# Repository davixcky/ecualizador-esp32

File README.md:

# Ecualizador de audio de tres bandas con ESP32

## Prototipo en protoboard

[Guía de montaje y esquema (PDF)](docs/protoboard/guia-prototipo-protoboard.pdf) · [Lista de materiales (CSV)](docs/protoboard/materiales.csv) · [Conexiones pin por pin (CSV)](docs/protoboard/conexiones.csv). Incluye pruebas con generador y osciloscopio, y ampliación con ESP32, pantalla y NeoPixel. [Fuente LaTeX](docs/latex/prototipo-protoboard.tex).

## Video del dispositivo

[Ver video en Full HD](docs/video/ecualizador-animado.mp4) · [Escena de Blender y texturas](docs/video/ecualizador-blender.zip). Demo de 36 segundos con sonido: los deslizadores cambian el audio usando las respuestas SPICE del circuito. Pantalla y luces sincronizadas; apertura de la tapa imantada. Es una demo virtual, no una grabación del prototipo físico.

Proyecto de Electrónica II · Universidad de la Costa · Leo Rojas, David Orozco y Manuel Castilla.

La ruta de audio usa filtros activos y controles analógicos. El ESP32 lee los niveles y calcula una FFT para la pantalla Waveshare de **1,9 pulgadas, 170 × 320, ST7789V2**. El gabinete EQ / 03 tiene acabado grafito, cierre con cuatro pares de imanes y dos canales interiores para 12 NeoPixel.

| Entrega | Archivos actuales |
|---|---|
| Presentación en LaTeX | [PDF](docs/presentacion/presentacion-fase2.pdf) · [PowerPoint con notas](docs/presentacion/presentacion-fase2.pptx) · [PDF con notas](docs/presentacion/presentacion-notas.pdf) |
| Exposición con animaciones | [PowerPoint animado](docs/presentacion/presentacion-animada.pptx) · [PDF por pasos](docs/presentacion/presentacion-animada.pdf) · [Cómo presentar](docs/presentacion/LEEME.md) |
| Informe | [PDF](docs/informe-fase2.pdf) · [Word](docs/informe-fase2.docx) · [Markdown](docs/informe-fase2.md) |
| Fuentes editables en LaTeX | [Informe](docs/latex/informe.tex) · [Presentación Beamer](docs/latex/presentacion.tex) |
| Presentación corta de filtros | [PDF de 10 diapositivas](docs/presentacion/presentacion-filtros-hoy.pdf) · [PowerPoint con notas](docs/presentacion/presentacion-filtros-hoy.pptx) · [Fuente LaTeX](docs/latex/presentacion-filtros.tex) |
| Ensayo de hoy | [Generador y osciloscopio: guía](simulacion/velxio/DEMO-HOY.md) |
| Paquete para otro computador | [ZIP portátil: presentación, esquema y simulaciones](docs/exposicion-portable.zip) |
| Simulación en Velxio | [Abrir casos locales](simulacion/velxio/index.html) · [Instrucciones y alcance](simulacion/velxio/README.md) · [100 Hz](simulacion/velxio/filtros-100Hz.vlx) · [1 kHz](simulacion/velxio/filtros-1000Hz.vlx) · [8 kHz](simulacion/velxio/filtros-8000Hz.vlx) |
| Esquemático | [PDF](hardware/ecualizador.pdf) · [KiCad](hardware/ecualizador.kicad_sch) · [ERC](hardware/erc.rpt) |
| PCB de una cara D.2 | [Plano PDF](hardware/pcb-rev-D2.pdf) · [KiCad](hardware/ecualizador.kicad_pcb) · [DRC](hardware/drc.rpt) · [Montaje y puentes](hardware/una-cara/LEEME.md) · [BOM](hardware/fabricacion/bom.csv) |
| Modelos 3D | [Gabinete STEP](cad/ecualizador-gabinete.step) · [Piezas STL](cad/stl/) · [PCB STEP](hardware/3d/ecualizador-placa.step) · [PCB VRML](hardware/3d/ecualizador-placa.wrl) |
| Propuesta original y rúbrica | [Fase 1](docs/fase1/) |

## Estado de la revisión del 22 de octubre de 2026

- ERC: cero errores y cero advertencias. Las 59 redes coinciden pin a pin con la definición del circuito.
- DRC D.2: cero infracciones, cero pads sin conectar y cero diferencias con el esquema. El DRC comprueba las 59 redes mediante cobre inferior, plano de GND y 80 cables. Las comprobaciones y límites de montaje se documentan en [la guía](hardware/una-cara/LEEME.md).
- ngspice: 23 casos del diseño revisado cumplen sus criterios. El caso histórico de Fase 1 reproduce el valle que motivó la corrección. El macromodelo del operacional es una aproximación propia.
- Velxio: tres proyectos ejecutados con motor SPICE; predominan graves a 100 Hz, medios a 1 kHz y agudos a 8 kHz. Los filtros usan operacionales ideales. Un cuarto [ensayo animado de 12 NeoPixel](simulacion/velxio/led-animado.vlx) ejecuta código del ESP32; usa un patrón programado sin audio.
- Velxio integrado: entrada → filtros → detectores → ADC ESP32 → TFT ILI9341, usando QEMU. Se comprueba el predominio de cada banda con 100 Hz, 1 kHz y 8 kHz. FFT sin calibración de frecuencia; no incluye potencia ni adaptación LED. [Guía y modelos](simulacion/velxio/INTEGRADO.md).
- Firmware: compilación ESP32 correcta; 19 comprobaciones DSP y cinco comparaciones de dibujo por franjas correctas en el computador.
- El montaje físico, las mediciones con instrumentos y el requisito de más del 70 % de dispositivos adquiridos y conectados **siguen sin evidencia en este repositorio**.

Los [registros de validación](docs/validacion/) conservan los resultados. Los renders provienen del CAD y de KiCad; las pantallas se dibujan con el código de interfaz y datos de ejemplo.

## Pantalla e iluminación

J4 es un adaptador de ocho señales a 2,54 mm, no la huella GH1.25 de Waveshare. Conectar por **nombre de señal**, siguiendo la tabla del informe: VCC, GND, DIN, CLK, CS, DC, RST y BL. La interfaz trabaja en horizontal a 320 × 170.

GPIO25 controla la tira mediante un 74AHCT125 y 330 Ω. J5 lleva 5 V, DIN y GND. Se prevén dos tramos de 100 mm, seis LED por tramo, y canales de 102 × 10,6 × 3 mm con difusores. El brillo inicial es 32/255, fijo. La fuente prevista es de 5 V / 3 A por J6; **desconectar VBUS del USB cuando se usa esa fuente**. No alimentar los LED desde 3,3 V ni usar VREF como retorno.

## Reproducir los archivos

Los PDF usan el logo oficial CUC, rojo institucional y Red Hat Display, según el [manual consultado](img/marca/README.md). Las fuentes vigentes son los `.tex` (LuaLaTeX). El PowerPoint contiene imágenes de las diapositivas y notas; el texto se edita en LaTeX. El HTML anterior está archivado en `docs/archivo/`.

```sh
# TeX Live: latex-extra, lang-spanish, fonts-recommended, luatex; pandoc
# Python: pymupdf, python-pptx (para exportar PNG y PowerPoint)
bash herramientas/compilar_documentos.sh

# Firmware y pruebas en computador
pio run -d firmware
make -C firmware/test prueba pantallas

# Conectividad y simulación (ngspice, numpy, matplotlib)
python3 herramientas/verificar_netlist.py
.venv/bin/python herramientas/simulacion.py

# PCB de una cara: regenerar y verificar
python3 herramientas/generar_esquematico.py
python3 herramientas/generar_pcb.py
bash herramientas/exportar_fabricacion.sh

# CAD (CadQuery) y renders (Blender, KiCad)
.venv/bin/python herramientas/validar_cad.py
bash cad/generar.sh

# Repetir la comprobación web (Node y Playwright con Chromium)
node herramientas/validar_velxio.cjs
node herramientas/validar_led_velxio.cjs
```

Las vistas de ensamblaje y colores de bandas parten de C2-ABPR; la revisión EQ / 03 adopta acabado grafito, rotulación compacta y cierre magnético. Las cotas de pantalla, controles y conectores deben contrastarse con las piezas adquiridas antes de imprimir y montar.

La presentación incluye fragmentos del esquema real para explicar preamplificador, Sallen-Key, sumador y detector. Los PDF adjuntan el esquema, el plano D.2 y los proyectos Velxio. El enlace y el QR abren el editor; después se importa el caso `.vlx`. Ver [cierre magnético y cotas](cad/CIERRE-MAGNETICO.md).

La PCB D.2 organiza las etapas con el flujo Python/KiCad y Freerouting de medidor-energia-esp32: ESP32 a la derecha, operacionales por etapas y cableado identificado por colores. Usa una sola cara de cobre y puentes aislados. Los controles van en el panel y requieren las [cabeceras y cables de montaje](hardware/una-cara/LEEME.md). Los Gerbers de dos capas B.1 están archivados y no corresponden al montaje vigente.

### Placa única E.2 (propuesta, 33 alambres)

[E.2](hardware/E2-placa-unica/README.md) reduce los 80 tramos de D.2 a 33 alambres en una sola placa de una cara de 200 × 120 mm para el gabinete original. Usa plano de GND, componentes con las patas más abiertas para pasar pistas por debajo, y reasigna las secciones de los amplificadores y los GPIO. El firmware se compila con `pio run -e e2`. La alternativa de tres placas está en [E.1](hardware/E1-tres-placas/README.md).

### Montaje de los puentes

La cara superior lleva 29 puentes cortos (hasta 20 mm entre extremos). Los 51 cables restantes se montan aislados por debajo. El total sigue siendo 80 tramos; no se añade una capa de cobre. [La guía](hardware/PUENTES.md) y [el plano de cuatro páginas](hardware/pcb-rev-D2.pdf) indican la cara de cada conexión. Los arcos del render son orientativos: el montaje requiere comprobar separación, sujeción y continuidad.

### Prototipo de laboratorio con TL072CP (±12 V)

Para el montaje con los integrados disponibles: [guía PDF](docs/prototipo-tl072/guia-prototipo-TL072.pdf), [fuente LaTeX](docs/latex/prototipo-tl072.tex) y [paquete de conexiones y simulación](docs/prototipo-tl072/prototipo-TL072.zip). Utiliza cuatro TL072, salida de línea y medidas a 100 Hz, 1 kHz y 8 kHz. Es una variante analógica independiente del diseño MCP6004 de 3,3 V; sus salidas no se conectan directamente al ESP32.

Esquema completo del prototipo en una lámina A2: [PDF](docs/prototipo-tl072/esquema-completo-TL072.pdf) · [SVG editable](docs/prototipo-tl072/esquema-completo.svg). Incluido al final de la guía TL072.

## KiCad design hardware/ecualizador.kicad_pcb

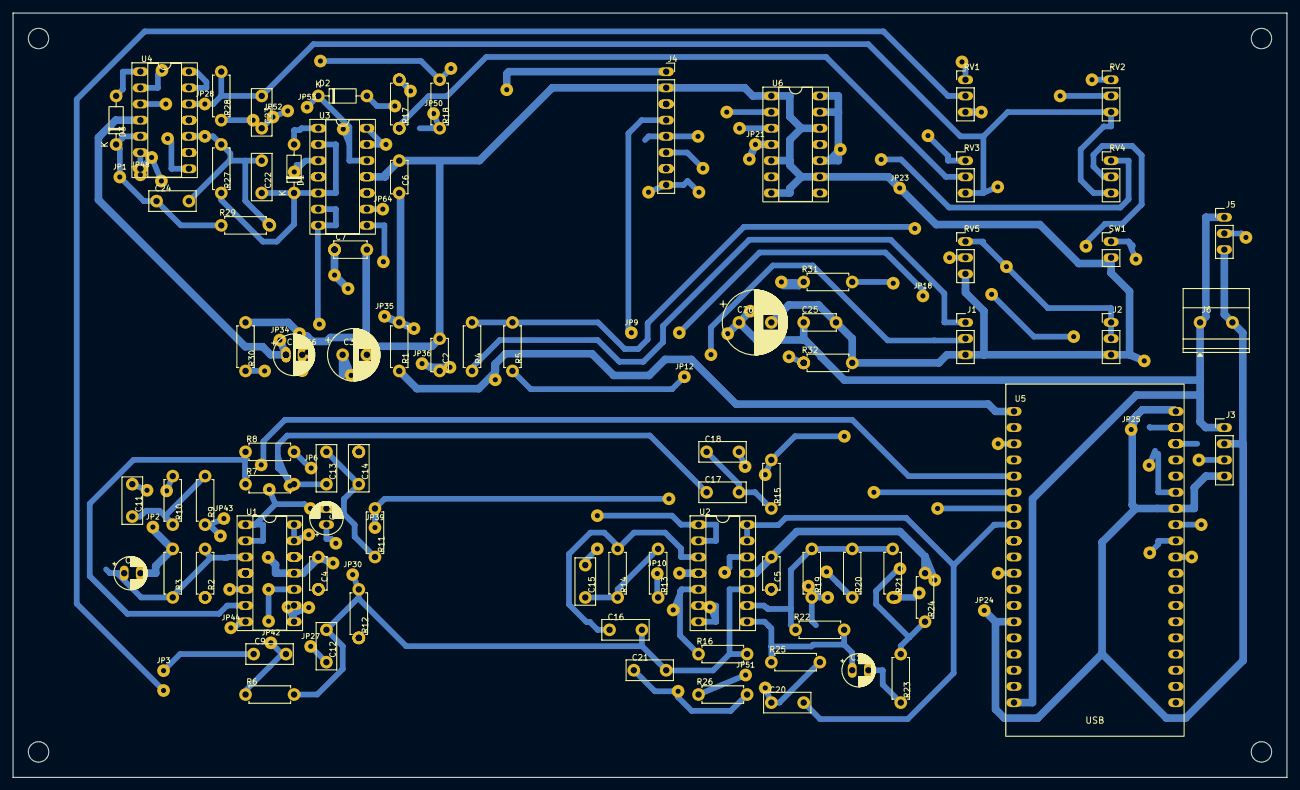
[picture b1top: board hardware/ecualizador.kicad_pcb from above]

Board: 2 copper layers, 200.0 x 120.0 mm, 162 parts (0 on the bottom side), 59 nets.

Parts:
C1: 100u 10V; UnaCara_C1
C2: 100n; UnaCara_C2
C3: 470u 10V; UnaCara_C3
C4: 100n; UnaCara_C4
C5: 100n; UnaCara_C5
C6: 100n; UnaCara_C6
C7: 100n; UnaCara_C7
C8: 10u 16V; UnaCara_C8
C9: 1u film; UnaCara_C9
C10: 10u 16V; UnaCara_C10
C11: 100n film; UnaCara_C11
C12: 47n film; UnaCara_C12
C13: 10n film; UnaCara_C13
C14: 10n film; UnaCara_C14
C15: 10n film; UnaCara_C15
C16: 4n7 film; UnaCara_C16
C17: 10n film; UnaCara_C17
C18: 10n film; UnaCara_C18
C19: 10u 16V; UnaCara_C19
C20: 4n7 film; UnaCara_C20
C21: 2n2 film; UnaCara_C21
C22: 100n film; UnaCara_C22
C23: 100n film; UnaCara_C23
C24: 100n film; UnaCara_C24
C25: 100n; UnaCara_C25
C26: 1000u 10V; UnaCara_C26
D1: 1N4148; UnaCara_D1
D2: 1N4148; UnaCara_D2
D3: 1N4148; UnaCara_D3
H1, H2, H3, H4: MountingHole_3.2mm_M3
J1: Entrada de línea 3,5 mm; UnaCara_J1
J2: Salida de línea 3,5 mm; UnaCara_J2
J3: PAM8403; UnaCara_J3
J4: Waveshare 1.9 ST7789V2; UnaCara_J4
J5: NeoPixel 5V DIN GND; UnaCara_J5
J6: Entrada 5V 3A; UnaCara_J6
JP1, JP2, JP3, JP4, JP5, JP6, JP7, JP8, JP9, JP10, JP11, JP12, JP13, JP14, JP15, JP16, JP17, JP18, JP19, JP20, JP21, JP22, JP23, JP24, JP25, JP26, JP27, JP28, JP29, JP30, JP31, JP32, JP33, JP34, JP35, JP36, JP37, JP38, JP39, JP40, JP41, JP42, JP43, JP44, JP45, JP46, JP47, JP48, JP49, JP50, JP51, JP52, JP53, JP54, JP55, JP56, JP57, JP58, JP59, JP60, JP61, JP62, JP63, JP64, JP65, JP66: Puente aislado
JP67, JP68, JP69, JP70, JP71, JP72, JP73, JP74, JP75, JP76, JP77, JP78, JP79: Puente a terminal
R1: 10; UnaCara_R1
R2: 10k 1%; UnaCara_R2
R3: 10k 1%; UnaCara_R3
R4: 10k; UnaCara_R4
R5: 10k; UnaCara_R5
R6: 100k; UnaCara_R6
R7: 22k 1%; UnaCara_R7
R8: 10k 1%; UnaCara_R8
R9: 10k 1%; UnaCara_R9
R10: 10k 1%; UnaCara_R10
R11: 27k 1%; UnaCara_R11
R12: 56k 1%; UnaCara_R12
R13: 10k 1%; UnaCara_R13
R14: 10k 1%; UnaCara_R14
R15: 2k7 1%; UnaCara_R15
R16: 5k6 1%; UnaCara_R16
R17: 47k 1%; UnaCara_R17
R18: 47k 1%; UnaCara_R18
R19: 47k 1%; UnaCara_R19
R20: 47k 1%; UnaCara_R20
R21: 47k 1%; UnaCara_R21
R22: 100k 1%; UnaCara_R22
R23: 100; UnaCara_R23
R24: 47k; UnaCara_R24
R25: 10k 1%; UnaCara_R25
R26: 10k 1%; UnaCara_R26
R27: 220k; UnaCara_R27
R28: 220k; UnaCara_R28
R29: 220k; UnaCara_R29
R30: 10k; UnaCara_R30
R31: 330; UnaCara_R31
R32: 10k; UnaCara_R32
RV1: 10k log; UnaCara_RV1
RV2: 10k lin; UnaCara_RV2
RV3: 10k lin; UnaCara_RV3
RV4: 10k lin; UnaCara_RV4
RV5: 10k log; UnaCara_RV5
SW1: Pulsador; UnaCara_SW1
U1: MCP6004; UnaCara_U1
U2: MCP6004; UnaCara_U2
U3: MCP6004; UnaCara_U3
U4: MCP6004; UnaCara_U4
U5: ESP32-DevKitC V4; UnaCara_U5
U6: 74AHCT125; UnaCara_U6

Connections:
+3.3VA: C1.1, C2.1, C4.1, C5.1, C6.1, C7.1, JP34.1, JP35.1, JP36.1, JP37.1, JP70.1, JP71.1, JP72.1, JP73.1, JP74.1, R1.2, R2.1, U1.4, U2.4, U3.4, U4.4
+3V3: J4.1, JP54.1, R1.1, U5.1
+5V: C3.1, C25.1, C26.1, J3.1, J5.1, J6.1, JP20.1, JP21.1, JP63.1, U5.19, U6.4, U6.10, U6.13, U6.14
/ADC_A: JP48.1, JP49.1, U4.6, U4.7, U5.7
/ADC_FFT: C20.2, U2.13, U2.14, U5.8
/ADC_G: JP5.1, U3.6, U3.7, U5.5
/ADC_M: JP60.1, U3.13, U3.14, U5.6
/AGUDOS: JP13.1, JP33.1, R15.2, RV4.1, U2.6, U2.7
/AMP_IN: J3.3, JP38.1, RV5.2
/A_W: JP17.1, JP40.1, R21.1, RV4.2, U4.3
/BTN: JP62.1, SW1.1, U5.11
/EQ_OUT: C19.1, R22.2, R25.1, U2.8
/GRAVES: C11.2, JP45.1, JP46.1, RV2.1, U1.8, U1.9
/G_W: JP59.1, JP65.1, R19.1, RV2.2, U3.3
/IN_L: J1.T, R4.1
/IN_R: J1.R, JP12.1, R5.1
/LED_5V: JP47.1, R31.1, U6.3
/LED_DATA: JP61.1, JP76.1, R32.1, U5.9, U6.2
/LED_DIN: J5.2, JP14.1, R31.2
/LINEA: J2.R, J2.T, JP15.1, R23.2, R24.1, RV5.1
/MEDIOS: C15.2, JP8.1, RV3.1, U2.1, U2.2
/MED_HP: JP10.1, JP39.1, R11.2, R13.1, U1.13, U1.14
/M_INV: JP4.1, JP32.1, R18.2, R20.1, U4.8
/M_W: JP77.1, R17.1, RV3.2, U3.10
/PRE: C13.1, C17.1, JP43.1, JP44.1, R7.2, R9.1, U1.7
/TFT_BL: J4.8, JP57.1, JP58.1, R30.1, U5.27
/TFT_CS: J4.5, JP55.1, U5.29
/TFT_DC: J4.6, JP56.1, U5.25
/TFT_MOSI: J4.3, JP78.1, U5.21
/TFT_RST: J4.7, JP79.1, U5.22
/TFT_SCK: J4.4, JP9.1, JP18.1, JP19.1, U5.28
/VREF: C10.2, C12.2, C16.2, C21.2, C22.2, C23.2, C24.2, JP28.1, JP29.1, JP30.1, JP31.1, R6.2, R12.2, R16.2, R27.2, R28.2, R29.2, RV2.3, RV3.3, RV4.3, U1.1, U1.2, U2.10, U4.10, U4.12, U5.3
GND: C1.2, C2.2, C3.2, C4.2, C5.2, C6.2, C7.2, C8.2, C25.2, C26.2, J1.S, J2.S, J3.2, J3.4, J4.2, J5.3, J6.2, JP2.1, JP22.1, JP23.1, JP24.1, JP25.1, JP66.1, JP67.1, R3.2, R24.2, R30.2, R32.2, RV1.3, RV5.3, SW1.2, U1.11, U2.11, U3.11, U4.11, U5.14, U5.20, U5.26, U6.1, U6.5, U6.7, U6.9, U6.12
unnamed: C9.1, JP3.1, RV1.2
unnamed: C10.1, JP6.1, R8.2
unnamed: C11.1, R9.2, R10.1
unnamed: C13.2, C14.1, R11.1
unnamed: C15.1, R13.2, R14.1
unnamed: C17.2, C18.1, R15.1
unnamed: C19.2, R23.1
unnamed: C20.1, JP51.1, R25.2, R26.1
unnamed: D1.2, U3.1
unnamed: C22.1, D1.1, R27.1, U3.2, U3.5
unnamed: D2.2, JP7.1, U3.8
unnamed: C23.1, D2.1, JP52.1, JP53.1, JP64.1, R28.1, U3.9, U3.12
unnamed: D3.2, U4.1
unnamed: C24.1, D3.1, JP1.1, R29.1, U4.2, U4.5
unnamed: JP16.1, R4.2, R5.2, RV1.1
unnamed: C8.1, R2.2, R3.1, U1.3
unnamed: C9.2, JP42.1, R6.1, U1.5
unnamed: R7.1, R8.1, U1.6
unnamed: C12.1, JP26.1, JP27.1, R10.2, U1.10
unnamed: C14.2, JP68.1, JP69.1, R12.1, U1.12
unnamed: C16.1, R14.2, U2.3
unnamed: C18.2, JP41.1, R16.1, U2.5
unnamed: R19.2, R20.2, R21.2, R22.1, U2.9
unnamed: C21.1, JP11.1, R26.2, U2.12
unnamed: JP50.1, JP75.1, R17.2, R18.1, U4.9
unnamed: U4.13, U4.14

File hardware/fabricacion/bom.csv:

"Reference","Value","Footprint","QUANTITY"
"C1","100u 10V","Ecualizador:UnaCara_C1","1"
"C2","100n","Ecualizador:UnaCara_C2","1"
"C3","470u 10V","Ecualizador:UnaCara_C3","1"
"C4","100n","Ecualizador:UnaCara_C4","1"
"C5","100n","Ecualizador:UnaCara_C5","1"
"C6","100n","Ecualizador:UnaCara_C6","1"
"C7","100n","Ecualizador:UnaCara_C7","1"
"C8","10u 16V","Ecualizador:UnaCara_C8","1"
"C9","1u film","Ecualizador:UnaCara_C9","1"
"C10","10u 16V","Ecualizador:UnaCara_C10","1"
"C11","100n film","Ecualizador:UnaCara_C11","1"
"C12","47n film","Ecualizador:UnaCara_C12","1"
"C13","10n film","Ecualizador:UnaCara_C13","1"
"C14","10n film","Ecualizador:UnaCara_C14","1"
"C15","10n film","Ecualizador:UnaCara_C15","1"
"C16","4n7 film","Ecualizador:UnaCara_C16","1"
"C17","10n film","Ecualizador:UnaCara_C17","1"
"C18","10n film","Ecualizador:UnaCara_C18","1"
"C19","10u 16V","Ecualizador:UnaCara_C19","1"
"C20","4n7 film","Ecualizador:UnaCara_C20","1"
"C21","2n2 film","Ecualizador:UnaCara_C21","1"
"C22","100n film","Ecualizador:UnaCara_C22","1"
"C23","100n film","Ecualizador:UnaCara_C23","1"
"C24","100n film","Ecualizador:UnaCara_C24","1"
"C25","100n","Ecualizador:UnaCara_C25","1"
"C26","1000u 10V","Ecualizador:UnaCara_C26","1"
"D1","1N4148","Ecualizador:UnaCara_D1","1"
"D2","1N4148","Ecualizador:UnaCara_D2","1"
"D3","1N4148","Ecualizador:UnaCara_D3","1"
"J1","Entrada de línea 3,5 mm","Ecualizador:UnaCara_J1","1"
"J2","Salida de línea 3,5 mm","Ecualizador:UnaCara_J2","1"
"J3","PAM8403","Ecualizador:UnaCara_J3","1"
"J4","Waveshare 1.9 ST7789V2","Ecualizador:UnaCara_J4","1"
"J5","NeoPixel 5V DIN GND","Ecualizador:UnaCara_J5","1"
"J6","Entrada 5V 3A","Ecualizador:UnaCara_J6","1"
"R1","10","Ecualizador:UnaCara_R1","1"
"R2","10k 1%","Ecualizador:UnaCara_R2","1"
"R3","10k 1%","Ecualizador:UnaCara_R3","1"
"R4","10k","Ecualizador:UnaCara_R4","1"
"R5","10k","Ecualizador:UnaCara_R5","1"
"R6","100k","Ecualizador:UnaCara_R6","1"
"R7","22k 1%","Ecualizador:UnaCara_R7","1"
"R8","10k 1%","Ecualizador:UnaCara_R8","1"
"R9","10k 1%","Ecualizador:UnaCara_R9","1"
"R10","10k 1%","Ecualizador:UnaCara_R10","1"
"R11","27k 1%","Ecualizador:UnaCara_R11","1"
"R12","56k 1%","Ecualizador:UnaCara_R12","1"
"R13","10k 1%","Ecualizador:UnaCara_R13","1"
"R14","10k 1%","Ecualizador:UnaCara_R14","1"
"R15","2k7 1%","Ecualizador:UnaCara_R15","1"
"R16","5k6 1%","Ecualizador:UnaCara_R16","1"
"R17","47k 1%","Ecualizador:UnaCara_R17","1"
"R18","47k 1%","Ecualizador:UnaCara_R18","1"
"R19","47k 1%","Ecualizador:UnaCara_R19","1"
"R20","47k 1%","Ecualizador:UnaCara_R20","1"
"R21","47k 1%","Ecualizador:UnaCara_R21","1"
"R22","100k 1%","Ecualizador:UnaCara_R22","1"
"R23","100","Ecualizador:UnaCara_R23","1"
"R24","47k","Ecualizador:UnaCara_R24","1"
"R25","10k 1%","Ecualizador:UnaCara_R25","1"
"R26","10k 1%","Ecualizador:UnaCara_R26","1"
"R27","220k","Ecualizador:UnaCara_R27","1"
"R28","220k","Ecualizador:UnaCara_R28","1"
"R29","220k","Ecualizador:UnaCara_R29","1"
"R30","10k","Ecualizador:UnaCara_R30","1"
"R31","330","Ecualizador:UnaCara_R31","1"
"R32","10k","Ecualizador:UnaCara_R32","1"
"RV1","10k log","Ecualizador:UnaCara_RV1","1"
"RV2","10k lin","Ecualizador:UnaCara_RV2","1"
"RV3","10k lin","Ecualizador:UnaCara_RV3","1"
"RV4","10k lin","Ecualizador:UnaCara_RV4","1"
"RV5","10k log","Ecualizador:UnaCara_RV5","1"
"SW1","Pulsador","Ecualizador:UnaCara_SW1","1"
"U1","MCP6004","Ecualizador:UnaCara_U1","1"
"U2","MCP6004","Ecualizador:UnaCara_U2","1"
"U3","MCP6004","Ecualizador:UnaCara_U3","1"
"U4","MCP6004","Ecualizador:UnaCara_U4","1"
"U5","ESP32-DevKitC V4","Ecualizador:UnaCara_U5","1"
"U6","74AHCT125","Ecualizador:UnaCara_U6","1"

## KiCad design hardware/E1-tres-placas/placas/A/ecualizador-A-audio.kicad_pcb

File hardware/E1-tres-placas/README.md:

# E.1 · Tres placas de una cara (alternativa)

El circuito de D.2 se reparte en tres placas CNC de una cara unidas por cables. Las tres pasan el DRC con 0 errores y 0 conexiones abiertas, y las netlists coinciden pin a pin con el esquema (59 redes).

| Placa | Tamaño (mm) | Puentes | Alambres directos | Total |
|---|---|---|---|---|
| A · audio | 110 × 78 | 21 | 9 | 30 |
| B · detectores | 70 × 55 | 5 | 4 | 9 |
| C · control | 100 × 75 | 5 | 0 | 5 |

En total son 44 alambres más los 15 cables entre placas de [`cables-entre-placas.csv`](cables-entre-placas.csv). Las tres placas necesitan un gabinete ampliado (220 × 143 mm por fuera), cuyas vistas están en `vistas/`.

Las placas se generan con `herramientas/tres_placas/`. Para la entrega se prefiere E.2: una sola placa, 33 alambres y el gabinete original.

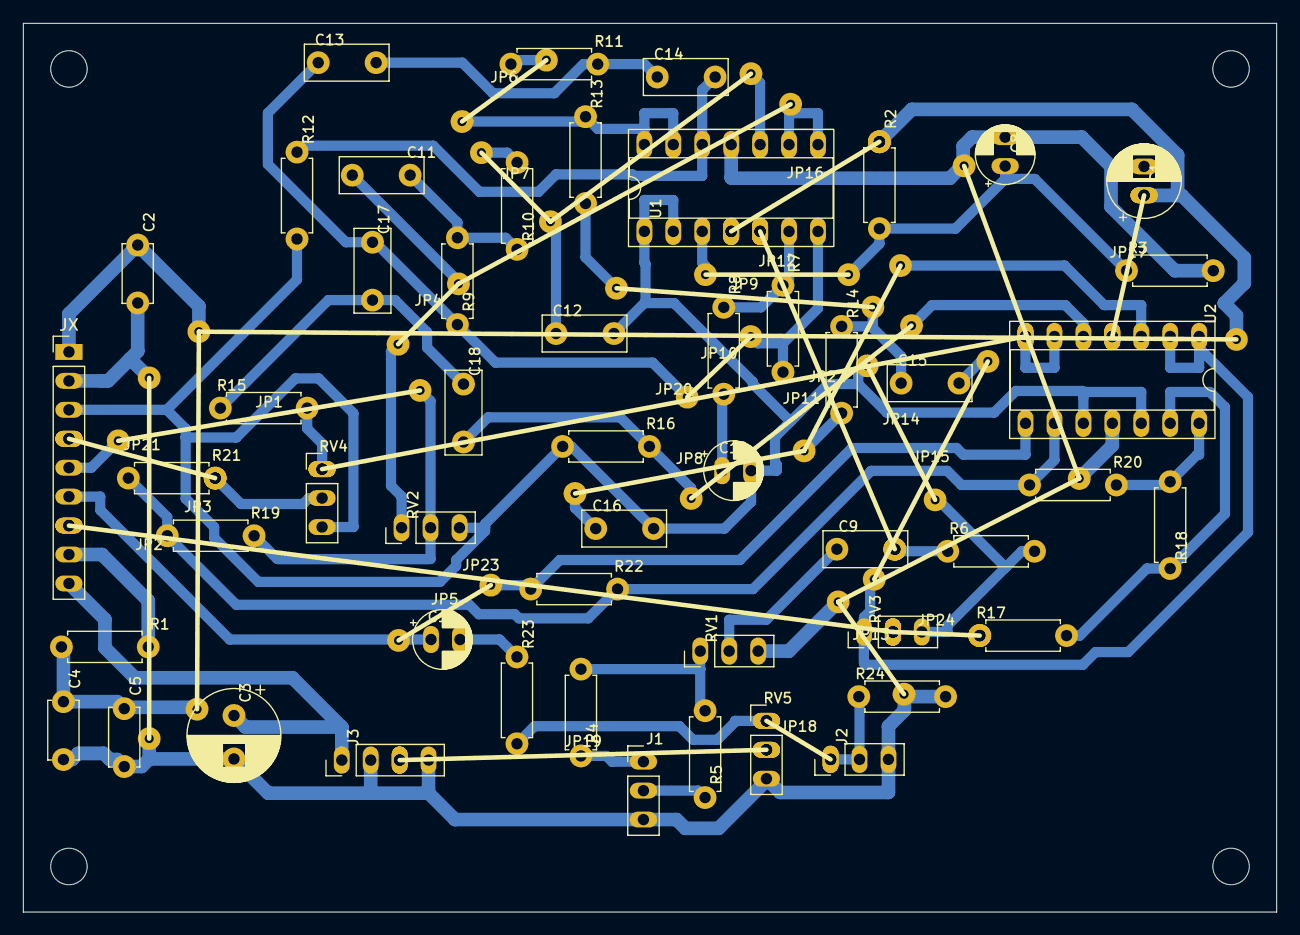
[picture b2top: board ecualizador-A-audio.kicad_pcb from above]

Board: 2 copper layers, 110.0 x 78.0 mm, 80 parts (0 on the bottom side), 36 nets.

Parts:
C1: 100u 10V; UnaCara_C1
C2: 100n; UnaCara_C2
C3: 470u 10V; UnaCara_C3
C4: 100n; UnaCara_C4
C5: 100n; UnaCara_C5
C8: 10u 16V; UnaCara_C8
C9: 1u film; UnaCara_C9
C10: 10u 16V; UnaCara_C10
C11: 100n film; UnaCara_C11
C12: 47n film; UnaCara_C12
C13: 10n film; UnaCara_C13
C14: 10n film; UnaCara_C14
C15: 10n film; UnaCara_C15
C16: 4n7 film; UnaCara_C16
C17: 10n film; UnaCara_C17
C18: 10n film; UnaCara_C18
C19: 10u 16V; UnaCara_C19
H1, H2, H3, H4: MountingHole_3.2mm_M3
J1: Entrada de línea 3,5 mm; UnaCara_J1
J2: Salida de línea 3,5 mm; UnaCara_J2
J3: PAM8403; UnaCara_J3
JP1, JP2, JP3, JP4, JP5, JP6, JP7, JP8, JP9, JP10, JP11, JP12, JP13, JP14, JP15, JP16, JP17, JP18, JP19, JP20, JP21, JP22, JP23, JP24: puente; Puente_alambre
JX: Conector entre placas; PinHeader_1x09_P2.54mm_Vertical
R1: 10; UnaCara_R1
R2: 10k 1%; UnaCara_R2
R3: 10k 1%; UnaCara_R3
R4: 10k; UnaCara_R4
R5: 10k; UnaCara_R5
R6: 100k; UnaCara_R6
R7: 22k 1%; UnaCara_R7
R8: 10k 1%; UnaCara_R8
R9: 10k 1%; UnaCara_R9
R10: 10k 1%; UnaCara_R10
R11: 27k 1%; UnaCara_R11
R12: 56k 1%; UnaCara_R12
R13: 10k 1%; UnaCara_R13
R14: 10k 1%; UnaCara_R14
R15: 2k7 1%; UnaCara_R15
R16: 5k6 1%; UnaCara_R16
R17: 47k 1%; UnaCara_R17
R18: 47k 1%; UnaCara_R18
R19: 47k 1%; UnaCara_R19
R20: 47k 1%; UnaCara_R20
R21: 47k 1%; UnaCara_R21
R22: 100k 1%; UnaCara_R22
R23: 100; UnaCara_R23
R24: 47k; UnaCara_R24
RV1: 10k log; UnaCara_RV1
RV2: 10k lin; UnaCara_RV2
RV3: 10k lin; UnaCara_RV3
RV4: 10k lin; UnaCara_RV4
RV5: 10k log; UnaCara_RV5
U1: MCP6004; UnaCara_U1
U2: MCP6004; UnaCara_U2

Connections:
+3.3VA: C1.1, C2.1, C4.1, C5.1, JP3.1, JP16.1, JP17.1, JX.1, R1.2, R2.1, U1.4, U2.4
+3V3: JX.8, R1.1
+5V: C3.1, J3.1, JX.9
/AGUDOS: JP20.1, R15.2, RV4.1, U2.6, U2.7
/AMP_IN: J3.3, JP19.1, RV5.2
/A_W: JP21.1, JX.4, R21.1, RV4.2
/EQ_OUT: C19.1, JP5.1, JX.6, R22.2, U2.8
/GRAVES: C11.2, JP4.1, RV2.1, U1.8, U1.9
/G_W: JP1.1, JX.5, R19.1, RV2.2
/IN_L: J1.T, R4.1
/IN_R: J1.R, R5.1
/LINEA: J2.R, J2.T, JP18.1, R23.2, R24.1, RV5.1
/MEDIOS: C15.2, JP15.1, RV3.1, U2.1, U2.2
/MED_HP: JP6.1, R11.2, R13.1, U1.13, U1.14
/M_INV: R18.2, R20.1, U2.14
/M_W: JP23.1, JP24.1, JX.7, R17.1, RV3.2
/PRE: C13.1, C17.1, JP10.1, R7.2, R9.1, U1.7
/VREF: C10.2, C12.2, C16.2, JP14.1, JX.3, R6.2, R12.2, R16.2, RV2.3, RV3.3, RV4.3, U1.1, U1.2, U2.10, U2.12
GND: C1.2, C2.2, C3.2, C4.2, C5.2, C8.2, J1.S, J2.S, J3.2, J3.4, JP2.1, JP13.1, JX.2, R3.2, R24.2, RV1.3, RV5.3, U1.11, U2.11
unnamed: C9.1, RV1.2
unnamed: C10.1, R8.2
unnamed: C11.1, R9.2, R10.1
unnamed: C13.2, C14.1, R11.1
unnamed: C15.1, JP9.1, R13.2, R14.1
unnamed: C17.2, C18.1, R15.1
unnamed: C19.2, R23.1
unnamed: R4.2, R5.2, RV1.1
unnamed: C8.1, JP12.1, R2.2, R3.1, U1.3
unnamed: C9.2, JP22.1, R6.1, U1.5
unnamed: R7.1, R8.1, U1.6
unnamed: C12.1, JP7.1, R10.2, U1.10
unnamed: C14.2, R12.1, U1.12
unnamed: C16.1, JP8.1, R14.2, U2.3
unnamed: C18.2, JP11.1, R16.1, U2.5
unnamed: R19.2, R20.2, R21.2, R22.1, U2.9
unnamed: R17.2, R18.1, U2.13

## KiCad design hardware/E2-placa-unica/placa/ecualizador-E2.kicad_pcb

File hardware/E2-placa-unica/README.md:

# E.2 · Placa única de una cara

PCB de una cara para la CNC del taller. Usa el mismo circuito, el mismo contorno y los mismos agujeros que D.2, y cabe en el gabinete original.

| | D.2 | E.1 (tres placas) | **E.2** |
|---|---|---|---|
| Placas | 1 | 3 | **1** |
| Alambres | 80 | 44 + 15 cables entre placas | **33** |

DRC: 0 errores y 0 conexiones abiertas. Los avisos de serigrafía se deben a las líneas que dibujan los puentes.

## Dimensiones

| | mm |
|---|---|
| Contorno | 200 × 120, espesor 1,6, cobre solo en B.Cu |
| Agujeros de montaje | 4 × Ø3,2 (M3) en (4, 4), (196, 4), (4, 116) y (196, 116); 192 × 112 entre centros |
| Taladros | 0,8 (puentes), 1,0 (terminales), 3,2 (montaje) |
| Pistas | 0,9 (alimentación 1,0); separación mínima 1,0 |
| Borde | El plano de GND queda a 1,0 mm del borde |
| Gabinete D.2 | Interior 203 × 123; exterior 208 × 128 (radio 8); 16,4 mm libres sobre la placa |

## Qué cambia respecto a D.2

1. **Pistas bajo los componentes.** Las resistencias y los diodos usan una separación de 10,16 mm y los cerámicos de 100 nF, de 7,5 mm. Son las mismas piezas con las patas más abiertas.
2. **Plano de GND.** El cobre libre es GND; en la CNC solo se fresa el contorno de las pistas.
3. **Asignación de pines** (el circuito es equivalente, verificado contra la netlist):
   - **Secciones del MCP6004.** U1–U4 son idénticos y las secciones se reparten entre ellos así:

     | Ubicación | Función |
     |---|---|
     | U1A | Filtro de graves (antes en U1C) |
     | U1C | Seguidor de VREF (antes en U1A) |
     | U2C | Antialiasing (antes en U2D) |
     | U2D | Sumador de salida (antes en U2C) |
     | U3A | Detector de medios (antes en U3C) |
     | U3B | Sección libre, como seguidor de VREF (antes en U4D) |
     | U3C | Inversor M_INV (antes en U4C) |
     | U3D | Detector de graves (antes en U3A) |
     | U4C | Seguidor ADC_M (antes en U3D) |
     | U4D | Seguidor ADC_G (antes en U3B) |

     Las demás secciones no cambian.
   - **ESP32.** Ver la tabla siguiente. El firmware se compila con `pio run -e e2`.
   - **Conectores de cable** (potenciómetros, jacks, PAM8403, NeoPixel, pulsador y pantalla). El orden de los pines cambia, pero cada pin lleva su etiqueta en la serigrafía. **Conecte cada cable según la etiqueta, no según la posición.** La lista está en [`etiquetas-conectores.csv`](etiquetas-conectores.csv).

| Señal | D.2 | E.2 |
|---|---|---|
| VREF (ADC) | GPIO36 | GPIO32 |
| ADC_M (medios) | GPIO35 | GPIO36 |
| ADC_A (agudos) | GPIO32 | GPIO39 |
| ADC_G / ADC_FFT | 34 / 33 | 34 / 33 (sin cambio) |
| TFT_CS / DC / RST | 5 / 21 / 22 | 25 / 22 / 5 |
| TFT_SCK / MOSI / BL | 18 / 23 / 19 | sin cambio |
| NeoPixel | 25 | 21 |
| Pulsador | 27 | 4 |

## Alambres

[`alambres.csv`](alambres.csv) lista los 33 alambres con su red, sus extremos y su longitud (de 5 a 38 mm; la mayoría mide menos de 20 mm).

- **20 puentes** (JP1–JP20) entre agujeros propios del puente.
- **13 enlaces de GND** pad a pad, que unen islas del plano. Sus agujeros coinciden con terminales existentes y se taladran una sola vez.

Los de menos de 15 mm pueden hacerse con patas recortadas de resistencias; los demás, con alambre aislado.

## Archivos

- `placa/`: placa KiCad (`ecualizador-E2.kicad_pcb`), proyecto, DRC y listas de puentes en JSON.
- `fabricacion/`: Gerber de B.Cu y Edge.Cuts, taladros sin duplicados, cobre 1:1 en PDF y plano de montaje.
- `vistas/`: cobre, montaje, cobre con alambres y renders 3D.
- `colocacion.json`: colocación y asignación de pines. Con ella se regenera la placa mediante `herramientas/placa_unica/`.

## Regenerar

```sh
cd herramientas/placa_unica
CONGND=1 CL=1.0 VIA_COST=60 python3 rutear3.py ../../hardware/E2-placa-unica/colocacion.json /tmp/e2-ruteo
python3 cerrar2.py /tmp/e2-ruteo /tmp/e2-final
python3 finalizar.py /tmp/e2-final ../../hardware/E2-placa-unica/colocacion.json /tmp/e2-paquete
```

Freerouting no es determinista. Una nueva ejecución puede producir otra cantidad de alambres; la placa entregada es la que está en `placa/`.

## Pendiente de verificar

- No se ha fresado ni montado.
- No se ha comprobado en 3D el ajuste en el gabinete con la nueva posición de las piezas altas (C26 y el ESP32 sobre su zócalo).
- El firmware E.2 compila, pero no se ha probado en hardware.
- El esquemático (`ecualizador.kicad_sch`) mantiene la asignación lógica de D.2; la asignación física de E.2 es la de las tablas anteriores.

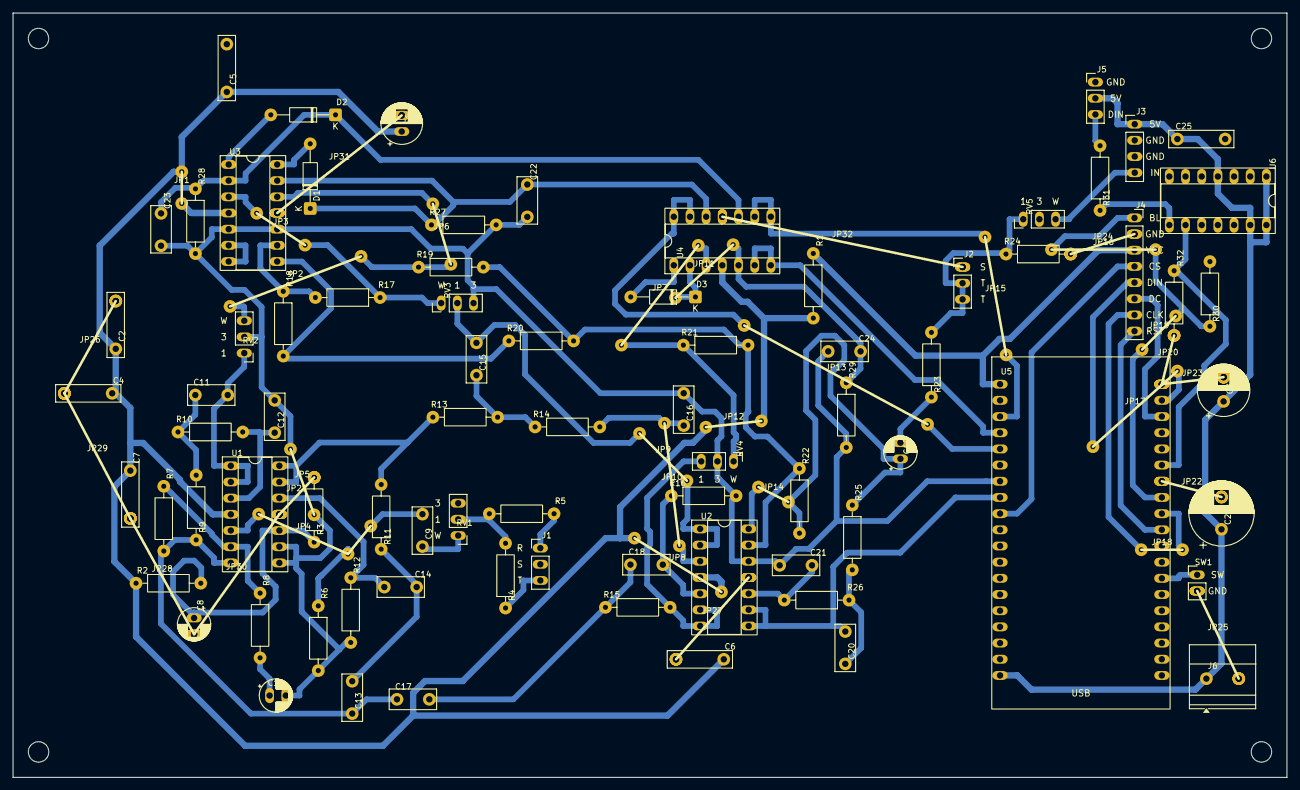
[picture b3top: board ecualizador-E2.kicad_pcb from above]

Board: 2 copper layers, 200.0 x 120.0 mm, 115 parts (0 on the bottom side), 59 nets.

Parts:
C1: 100u 10V; UnaCara_C1
C2, C4, C5, C6, C7, C25: 100n; C_Rect_L10.0mm_W2.5mm_P7.50mm_MKS4
C3: 470u 10V; UnaCara_C3
C8: 10u 16V; UnaCara_C8
C9: 1u film; UnaCara_C9
C10: 10u 16V; UnaCara_C10
C11: 100n film; UnaCara_C11
C12: 47n film; UnaCara_C12
C13: 10n film; UnaCara_C13
C14: 10n film; UnaCara_C14
C15: 10n film; UnaCara_C15
C16: 4n7 film; UnaCara_C16
C17: 10n film; UnaCara_C17
C18: 10n film; UnaCara_C18
C19: 10u 16V; UnaCara_C19
C20: 4n7 film; UnaCara_C20
C21: 2n2 film; UnaCara_C21
C22: 100n film; UnaCara_C22
C23: 100n film; UnaCara_C23
C24: 100n film; UnaCara_C24
C26: 1000u 10V; UnaCara_C26
D1, D2, D3: 1N4148; D_DO-35_SOD27_P10.16mm_Horizontal
H1, H2, H3, H4: MountingHole_3.2mm_M3
J1: Entrada de línea 3,5 mm; UnaCara_J1
J2: Salida de línea 3,5 mm; UnaCara_J2
J3: PAM8403; UnaCara_J3
J4: Waveshare 1.9 ST7789V2; UnaCara_J4
J5: NeoPixel 5V DIN GND; UnaCara_J5
J6: Entrada 5V 3A; UnaCara_J6
JP1, JP2, JP3, JP4, JP5, JP6, JP7, JP8, JP9, JP10, JP11, JP12, JP13, JP14, JP15, JP16, JP17, JP18, JP19, JP20, JP21, JP22, JP23, JP24, JP25, JP26, JP27, JP28, JP29, JP30, JP31, JP32: puente; Puente_alambre
R1: 10; R_Axial_DIN0207_L6.3mm_D2.5mm_P10.16mm_Horizontal
R2, R3, R8, R9, R10, R13, R14, R25, R26: 10k 1%; R_Axial_DIN0207_L6.3mm_D2.5mm_P10.16mm_Horizontal
R4, R5, R30, R32: 10k; R_Axial_DIN0207_L6.3mm_D2.5mm_P10.16mm_Horizontal
R6: 100k; R_Axial_DIN0207_L6.3mm_D2.5mm_P10.16mm_Horizontal
R7: 22k 1%; R_Axial_DIN0207_L6.3mm_D2.5mm_P10.16mm_Horizontal
R11: 27k 1%; R_Axial_DIN0207_L6.3mm_D2.5mm_P10.16mm_Horizontal
R12: 56k 1%; R_Axial_DIN0207_L6.3mm_D2.5mm_P10.16mm_Horizontal
R15: 2k7 1%; R_Axial_DIN0207_L6.3mm_D2.5mm_P10.16mm_Horizontal
R16: 5k6 1%; R_Axial_DIN0207_L6.3mm_D2.5mm_P10.16mm_Horizontal
R17, R18, R19, R20, R21: 47k 1%; R_Axial_DIN0207_L6.3mm_D2.5mm_P10.16mm_Horizontal
R22: 100k 1%; R_Axial_DIN0207_L6.3mm_D2.5mm_P10.16mm_Horizontal
R23: 100; R_Axial_DIN0207_L6.3mm_D2.5mm_P10.16mm_Horizontal
R24: 47k; R_Axial_DIN0207_L6.3mm_D2.5mm_P10.16mm_Horizontal
R27, R28, R29: 220k; R_Axial_DIN0207_L6.3mm_D2.5mm_P10.16mm_Horizontal
R31: 330; R_Axial_DIN0207_L6.3mm_D2.5mm_P10.16mm_Horizontal
RV1: 10k log; UnaCara_RV1
RV2: 10k lin; UnaCara_RV2
RV3: 10k lin; UnaCara_RV3
RV4: 10k lin; UnaCara_RV4
RV5: 10k log; UnaCara_RV5
SW1: Pulsador; UnaCara_SW1
U1: MCP6004; UnaCara_U1
U2: MCP6004; UnaCara_U2
U3: MCP6004; UnaCara_U3
U4: MCP6004; UnaCara_U4
U5: ESP32-DevKitC V4; UnaCara_U5
U6: 74AHCT125; UnaCara_U6

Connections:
+3.3VA: C1.1, C2.1, C4.1, C5.1, C6.1, C7.1, JP1.1, JP8.1, JP12.1, R1.2, R2.1, U1.4, U2.4, U3.4, U4.4
+3V3: J4.3, R1.1, U5.1
+5V: C3.1, C25.1, C26.1, J3.1, J5.2, J6.1, U5.19, U6.1, U6.4, U6.13, U6.14
/ADC_A: U4.6, U4.7, U5.4
/ADC_FFT: C20.2, U2.8, U2.9, U5.8
/ADC_G: JP13.1, U4.13, U4.14, U5.5
/ADC_M: JP15.1, U4.8, U4.9, U5.3
/AGUDOS: R15.2, RV4.3, U2.6, U2.7
/AMP_IN: J3.4, RV5.3
/A_W: JP7.1, R21.1, RV4.1, U4.3
/BTN: SW1.1, U5.32
/EQ_OUT: C19.1, JP14.1, R22.2, R25.1, U2.14
/GRAVES: C11.2, RV2.1, U1.1, U1.2
/G_W: JP2.1, JP6.1, R19.1, RV2.3, U3.12
/IN_L: J1.S, R4.1
/IN_R: J1.T, R5.1
/LED_5V: R31.1, U6.8
/LED_DATA: R32.1, U5.25, U6.9
/LED_DIN: J5.3, R31.2
/LINEA: J2.R, J2.S, R23.2, R24.1, RV5.1
/MEDIOS: C15.2, JP9.1, RV3.2, U2.1, U2.2
/MED_HP: R11.2, R13.1, U1.13, U1.14
/M_INV: R18.2, R20.1, U3.8
/M_W: JP3.1, R17.1, RV3.1, U3.3
/PRE: C13.1, C17.1, R7.2, R9.1, U1.7
/TFT_BL: J4.1, JP16.1, JP19.1, R30.1, U5.27
/TFT_CS: J4.4, U5.9
/TFT_DC: J4.6, U5.22
/TFT_MOSI: J4.5, JP17.1, U5.21
/TFT_RST: J4.8, U5.29
/TFT_SCK: J4.7, JP18.1, U5.28
/VREF: C10.2, C12.2, C16.2, C21.2, C22.2, C23.2, C24.2, JP5.1, R6.2, R12.2, R16.2, R27.2, R28.2, R29.2, RV2.2, RV3.3, RV4.2, U1.8, U1.9, U2.12, U3.5, U3.10, U5.7
GND: C1.2, C2.2, C3.2, C4.2, C5.2, C6.2, C7.2, C8.2, C25.2, C26.2, J1.R, J2.T, J3.2, J3.3, J4.2, J5.1, J6.2, JP20.1, JP21.1, JP22.1, JP23.1, JP24.1, JP25.1, JP26.1, JP27.1, JP28.1, JP29.1, JP30.1, JP31.1, JP32.1, R3.2, R24.2, R30.2, R32.2, RV1.3, RV5.2, SW1.2, U1.11, U2.11, U3.11, U4.11, U5.14, U5.20, U5.26, U6.2, U6.5, U6.7, U6.10, U6.12
unnamed: C9.1, RV1.1
unnamed: C10.1, R8.2
unnamed: C11.1, R9.2, R10.1
unnamed: C13.2, C14.1, R11.1
unnamed: C15.1, R13.2, R14.1
unnamed: C17.2, C18.1, R15.1
unnamed: C19.2, R23.1
unnamed: C20.1, R25.2, R26.1
unnamed: D1.2, U3.14
unnamed: C22.1, D1.1, R27.1, U3.13, U4.12
unnamed: D2.2, U3.1
unnamed: C23.1, D2.1, R28.1, U3.2, U4.10
unnamed: D3.2, U4.1
unnamed: C24.1, D3.1, JP11.1, R29.1, U4.2, U4.5
unnamed: R4.2, R5.2, RV1.2
unnamed: C8.1, R2.2, R3.1, U1.10
unnamed: C9.2, JP4.1, R6.1, U1.5
unnamed: R7.1, R8.1, U1.6
unnamed: C12.1, R10.2, U1.3
unnamed: C14.2, R12.1, U1.12
unnamed: C16.1, JP10.1, R14.2, U2.3
unnamed: C18.2, R16.1, U2.5
unnamed: R19.2, R20.2, R21.2, R22.1, U2.13
unnamed: C21.1, R26.2, U2.10
unnamed: R17.2, R18.1, U3.9
unnamed: U3.6, U3.7

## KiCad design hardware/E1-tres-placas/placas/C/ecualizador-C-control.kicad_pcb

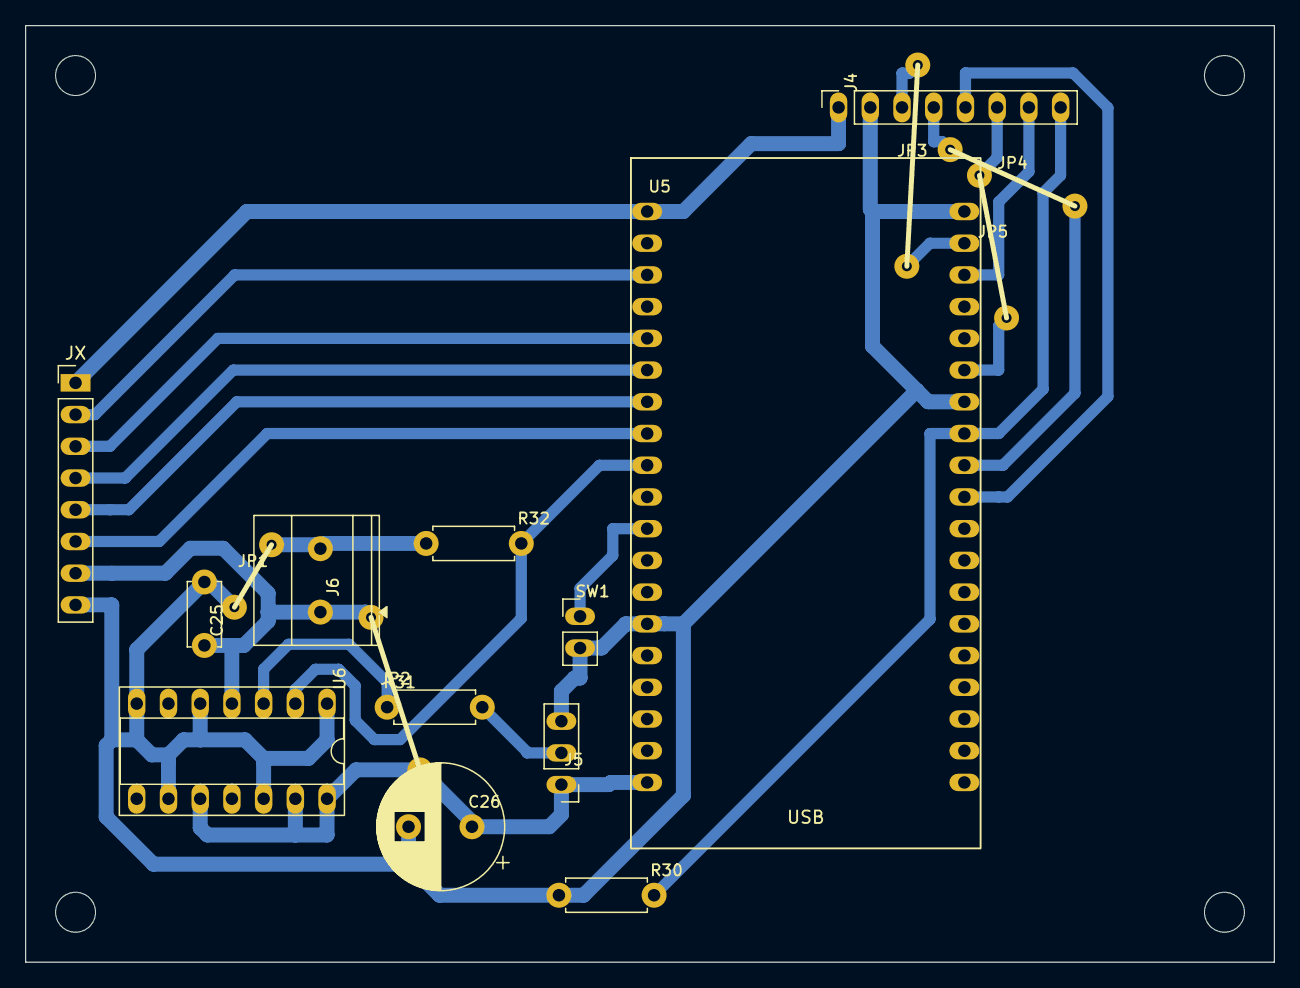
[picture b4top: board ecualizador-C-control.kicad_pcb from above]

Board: 2 copper layers, 100.0 x 75.0 mm, 21 parts (0 on the bottom side), 18 nets.

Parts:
C25: 100n; UnaCara_C25
C26: 1000u 10V; UnaCara_C26
H1, H2, H3, H4: MountingHole_3.2mm_M3
J4: Waveshare 1.9 ST7789V2; UnaCara_J4
J5: NeoPixel 5V DIN GND; UnaCara_J5
J6: Entrada 5V 3A; UnaCara_J6
JP1, JP2, JP3, JP4, JP5: puente; Puente_alambre
JX: Conector entre placas; PinHeader_1x08_P2.54mm_Vertical
R30: 10k; UnaCara_R30
R31: 330; UnaCara_R31
R32: 10k; UnaCara_R32
SW1: Pulsador; UnaCara_SW1
U5: ESP32-DevKitC V4; UnaCara_U5
U6: 74AHCT125; UnaCara_U6

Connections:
+3V3: J4.1, JX.1, U5.1
+5V: C25.1, C26.1, J5.1, J6.1, JP2.1, JX.7, U5.19, U6.4, U6.10, U6.13, U6.14
/ADC_A: JX.5, U5.7
/ADC_FFT: JX.6, U5.8
/ADC_G: JX.3, U5.5
/ADC_M: JX.4, U5.6
/BTN: SW1.1, U5.11
/LED_5V: R31.1, U6.3
/LED_DATA: R32.1, U5.9, U6.2
/LED_DIN: J5.2, R31.2
/TFT_BL: J4.8, R30.1, U5.27
/TFT_CS: J4.5, U5.29
/TFT_DC: J4.6, JP5.1, U5.25
/TFT_MOSI: J4.3, JP3.1, U5.21
/TFT_RST: J4.7, U5.22
/TFT_SCK: J4.4, JP4.1, U5.28
/VREF: JX.2, U5.3
GND: C25.2, C26.2, J4.2, J5.3, J6.2, JP1.1, JX.8, R30.2, R32.2, SW1.2, U5.14, U5.20, U5.26, U6.1, U6.5, U6.7, U6.9, U6.12

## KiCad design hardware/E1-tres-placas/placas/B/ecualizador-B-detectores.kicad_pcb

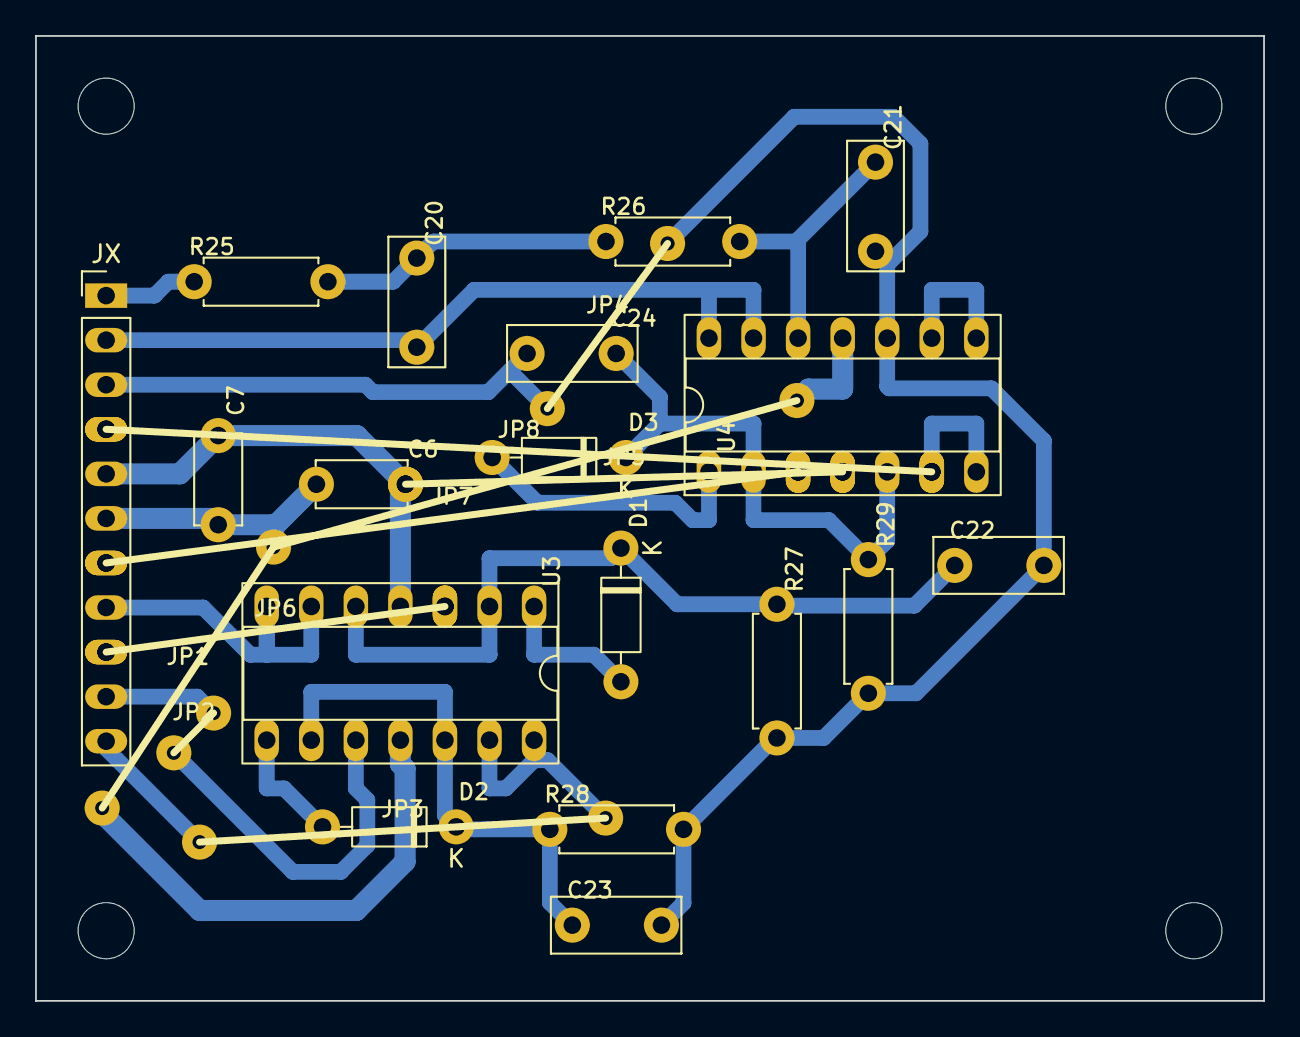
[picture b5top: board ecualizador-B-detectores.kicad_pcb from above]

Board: 2 copper layers, 70.0 x 55.0 mm, 30 parts (0 on the bottom side), 20 nets.

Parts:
C6: 100n; UnaCara_C6
C7: 100n; UnaCara_C7
C20: 4n7 film; UnaCara_C20
C21: 2n2 film; UnaCara_C21
C22: 100n film; UnaCara_C22
C23: 100n film; UnaCara_C23
C24: 100n film; UnaCara_C24
D1: 1N4148; UnaCara_D1
D2: 1N4148; UnaCara_D2
D3: 1N4148; UnaCara_D3
H1, H2, H3, H4: MountingHole_3.2mm_M3
JP1, JP2, JP3, JP4, JP5, JP6, JP7, JP8: puente; Puente_alambre
JX: Conector entre placas; PinHeader_1x11_P2.54mm_Vertical
R25: 10k 1%; UnaCara_R25
R26: 10k 1%; UnaCara_R26
R27: 220k; UnaCara_R27
R28: 220k; UnaCara_R28
R29: 220k; UnaCara_R29
U3: MCP6004; UnaCara_U3
U4: MCP6004; UnaCara_U4

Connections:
+3.3VA: C6.1, C7.1, JP5.1, JX.5, U3.4, U4.4
/ADC_A: JP8.1, JX.4, U4.6, U4.7
/ADC_FFT: C20.2, JX.2, U4.13, U4.14
/ADC_G: JX.8, U3.6, U3.7
/ADC_M: JP3.1, JX.11, U3.13, U3.14
/A_W: JP7.1, JX.7, U4.3
/EQ_OUT: JX.1, R25.1
/G_W: JP6.1, JX.9, U3.3
/M_W: JP2.1, JX.10, U3.10
/VREF: C21.2, C22.2, C23.2, C24.2, JP4.1, JX.3, R27.2, R28.2, R29.2, U4.10
GND: C6.2, C7.2, JP1.1, JX.6, U3.11, U4.11
unnamed: C20.1, R25.2, R26.1
unnamed: D1.2, U3.1
unnamed: C22.1, D1.1, R27.1, U3.2, U3.5
unnamed: D2.2, U3.8
unnamed: C23.1, D2.1, R28.1, U3.9, U3.12
unnamed: D3.2, U4.1
unnamed: C24.1, D3.1, R29.1, U4.2, U4.5
unnamed: C21.1, R26.2, U4.12
unnamed: U4.8, U4.9
